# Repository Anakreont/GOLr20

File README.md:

# GOLr20 - HF balloon tracker with a receiver (FT8 contacts + WSPR)

One project, three parts: **GOLr20** - the tracker board (marked "R20" on the PCB), **GOLkf** - its firmware,
**GOLbase** - the ground station program.

The idea: a pico balloon that makes ordinary FT8 contacts (answers callers like a normal station), stores them in a log,
sends the log down in FT8 data frames, accepts signed commands from the ground and also beacons WSPR for tracking.

**Status (2026-11-23): boards v0.2 are ordered, nothing has been built or powered up yet. Board files and firmware are complete
enough to build and flash one, but the receiver, the transmitter level and the whole concept are unproven on hardware.**

## Hardware v0.2 (`pcb_v0.2/`)
- `R20_v0_2_gerber.zip`, `BOM_R20_v0_2.csv`, `CPL_R20_v0_2.csv` - the files sent to JLCPCB (Economic PCBA, top side, 0.8 mm).
- `kicad_src/` - KiCad 7 board (`pcb/r20.kicad_pcb`) and the Python scripts that generate it: `projekt.py` (parts and nets - there is no drawn schematic), `uklad.py` (placement), `buduj.py`. Parts placement drawing: `img/r20_v0_2_parts.png`.
- MCU RP2354A (QFN-60), 12 MHz crystal, USB for flashing (BOOTSEL), no SWD pads.
- Core supply from an external 1.1 V LDO (U8, TLV74311P) instead of the on-chip switcher: no inductor, less switching noise next to the receiver.
  VREG_FB to ground, VREG_LX open, VREG_AVDD/VREG_VIN powered (RP2350 datasheet, external core supply).
- TX: Si5351A + 26 MHz TCXO, CLK0 through 100 nF to the ANT pad; pads for an optional low-pass filter (C24, C25 not fitted).
- RX: ANT -> SN74CBTLV3253 used as a 4-phase mixer driven by Si5351 CLK1/CLK2 -> TLV9062 differential amplifiers -> ADC (I and Q).
- GPS ATGM336H and the Si5351/TCXO are behind P-MOSFET power switches. 3.3 V from ME6211C33.
- Solar input with pads for a supercapacitor (SC+ / SC-) on the bottom; D1 (clamp) not fitted.
- Break-off PROG tab with a 2x3 pin header: B0, EN, V+, D+, D-, G.
- GPIO: GPS UART 8 (TX) / 9 (RX), I2C 16 / 17, receiver supply from GPIO19, ADC0-2 for I, Q and panel voltage.
- Not fitted by design: C24, C25, D1.

### Known issues of v0.2
- The first BOM had a 1.2 V regulator for the core (ME6211C12). RP2350 recommends 1.05-1.16 V (absolute max 1.21 V).
  The BOM here already has the 1.1 V part (C485147, same SOT-23-5 pinout).
- Only 1 uF at DVDD (datasheet suggests 4.7 uF at the far pin).
- JLCPCB adds two 1.15 mm tooling holes for assembly (one under the GPS module, one in the ground pour). They do not cut any track.

## Firmware: GOLkf v0.2 (`firmware_golkf/`)
- `rdzen/` - the logic core, hardware independent: energy levels from panel voltage and sun elevation, window plan (TX/RX),
  FT8 contact state machine, log, signed commands, WSPR schedule (Traquito channel maths), no-transmit zones.
- `sprzet/` - hardware layer for R20 (Pico SDK): Si5351 control, I/Q receiver + FT8 decoder, FT8/WSPR transmit, GPS, flash storage, USB console.
- `uf2/` - prebuilt images to copy onto the RP2350 drive.
- **[`firmware_golkf/FLASHING.md`](firmware_golkf/FLASHING.md) - how to build, flash and bring the board up.**

**The firmware compiles and its PC-side tests pass, but it has never run on a board.** There is no power saving yet.
The command key (16 bytes) is not in the code; set it from the console (the same key goes into GOLbase).

## Ground station: GOLbase (`ground_station/`)
The program that receives the balloon's log and sends it commands through an ordinary HF radio (Windows, Python, Polish UI).
Balloon contacts are written to an ADIF file; Log4OM is optional. See [`ground_station/README.md`](ground_station/README.md).
`protocol/robot_proto.py` is a copy of the frame and command format (version 1) for reference.

## `sim_m33/` - can an RP2350 decode FT8 in time?
kgoba/ft8_lib built for Cortex-M33 and run in QEMU (mps2-an505) on recorded audio, counting instructions.
Busy 20 m recording: 19 decodes with default settings; with 70 candidates / 20 LDPC iterations 18 decodes and
about 85 million instructions after the window, estimated 0.7-1.0 s on a 150 MHz RP2350 (an estimate, not a measurement).

## `power_budget/`
`bilans.py` - rough current budget for six 52 x 23 mm cells in series and a mass estimate. Component currents are typical
values, not measurements.

## Callsigns
The callsigns in the code are placeholders (`QQ0QQQ` for WSPR, `QQ0Q` for FT8). Set your own before transmitting; an amateur licence is required.

## Related
GOLt433, the 433 MHz LoRa camera tracker from the same author: https://github.com/Anakreont/GOLt433

## Licence
MIT (see `LICENSE`) for the code and the board files. Design by SQ9GOL. Source comments are in Polish.

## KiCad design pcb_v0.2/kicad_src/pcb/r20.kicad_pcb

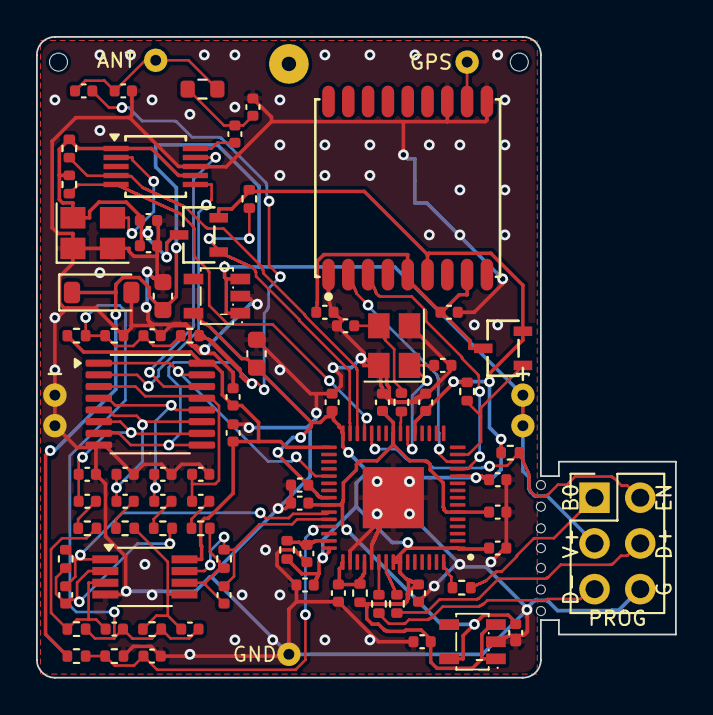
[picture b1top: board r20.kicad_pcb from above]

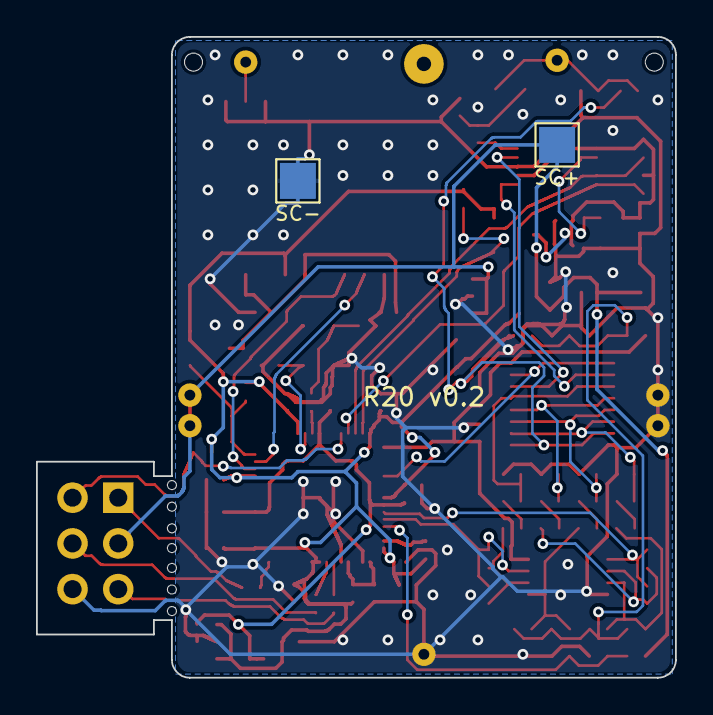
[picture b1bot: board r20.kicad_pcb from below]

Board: 2 copper layers, 35.5 x 35.6 mm, 99 parts (2 on the bottom side), 50 nets.

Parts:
ANT: (no value)
ANT_GND: (no value)
C1, C2: 10uF; C_0603_1608Metric
C3, C4, C5, C16, C22, C27, C37, C38, C40, C41, C42, C43: 1uF; C_0402_1005Metric
C6, C7, C8, C9, C10, C11, C12, C13, C14, C15, C20, C21, C23, C26, C28, C29, C30, C31, C36, C39: 100nF; C_0402_1005Metric
C17, C18: 15pF; C_0402_1005Metric
C24, C25: NC (filtr); C_0402_1005Metric
C32, C33, C34, C35: 47pF; C_0402_1005Metric
D1: NC BZT52C5V1 (ogr. 5,1 V, tylko pola); D_SOD-123
GPS_ANT: (no value)
H1, H2: (no value)
J1: PROG 2x3; PinHeader_2x03_P2.54mm_Vertical
L2: 0R (miejsce na cewke filtra); R_0603_1608Metric
MB1, MB2, MB3, MB4, MB5, MB6, MB7: (no value)
PV+, PV+2: (no value)
PV-, PV-2: (no value)
Q1: SI2301CDS (zas. Si5351 + TCXO); SI2301_SOT23
Q2: SI2301CDS (zas. GPS); SI2301_SOT23
R1, R2: 10R; R_0402_1005Metric
R3, R4, R16, R17, R20, R21: 1k; R_0402_1005Metric
R5, R13, R14: 10k; R_0402_1005Metric
R6, R7: 27R; R_0402_1005Metric
R8, R9, R18, R19, R22, R23: 1M; R_0402_1005Metric
R10, R15, R24: 100k; R_0402_1005Metric
R11, R12: 4.7k; R_0402_1005Metric
SC+: TestPoint_Pad_2.0x2.0mm
SC-: TestPoint_Pad_2.0x2.0mm
STAB: (no value)
U1: RP2354A (pamiec 2 MB w srodku); RP2354A_QFN-60
U3: SI5351A-B-GTR; MSOP-10_3x3mm_P0.5mm
U4: SN74CBTLV3253PWR; TSSOP-16_4.4x5mm_P0.65mm
U5: TLV9062IDGKR; VSSOP-8_3.0x3.0mm_P0.65mm
U6: ME6211C33M5G-N (3,3 V); ME6211_SOT23-5
U7: ATGM336H-5N31; ATGM336H
U8: ME6211C12M5G-N (rdzen 1,2 V); ME6211_SOT23-5
Y1: kwarc 12 MHz X322512MSB4SI; Crystal_SMD_3225-4Pin_3.2x2.5mm
Y2: TCXO 26 MHz KDS 1XTW26000MAA; Crystal_SMD_3225-4Pin_3.2x2.5mm

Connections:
+1V1: C4.1, C13.1, C14.1, C15.1, U1.6, U1.23, U1.39, U8.5
+3V3: C2.1, C3.1, C6.1, C7.1, C8.1, C9.1, C10.1, C11.1, C12.1, Q1.2, Q2.2, R1.1, R2.1, R5.2, R10.2, R24.2, U1.1, U1.11, U1.20, U1.30, U1.38, U1.45, U1.53, U1.54, U6.5, U7.6, U8.1, U8.3
ADC_AVDD: C16.1, R2.2, U1.44
ANT: ANT.1, C25.1, C26.1, L2.2
ANT_F: C23.2, C24.1, L2.1
BOOTSEL: J1.1, R4.2
GND: ANT_GND.1, C1.2, C2.2, C3.2, C4.2, C5.2, C6.2, C7.2, C8.2, C9.2, C10.2, C11.2, C12.2, C13.2, C14.2, C15.2, C16.2, C17.2, C18.2, C20.2, C21.2, C22.2, C24.2, C25.2, C27.2, C28.2, C29.2, C30.2, C31.2, C36.2, C37.2, C38.2, C39.2, D1.2, J1.6, PV-.1, PV-2.1, R9.2, R14.2, SC-.1, U1.47, U1.50, U1.61, U3.8, U4.8, U5.4, U6.2, U7.1, U7.10, U7.12, U8.2, Y1.2, Y1.4, Y2.1, Y2.2
GPS_ANT: GPS_ANT.1, U7.11
GPS_EN_N: Q2.1, R24.1, U1.14
GPS_RXD: U1.12, U7.3
GPS_TXD: U1.13, U7.2
GPS_VCC: C38.1, C39.1, Q2.3, U7.5, U7.8
I_N: C32.1, R17.2, R18.1, U5.2
I_P: C33.1, R16.2, R19.1, U5.3
LO_I: U3.9, U4.14
LO_Q: U3.6, U4.2
QA: C28.1, C40.1, U4.6, U4.10
QA_C: C40.2, R16.1
QB: C29.1, C42.1, U4.5, U4.11
QB_C: C42.2, R20.1
QC: C30.1, C41.1, U4.4, U4.12
QC_C: C41.2, R17.1
QD: C31.1, C43.1, U4.3, U4.13
QD_C: C43.2, R21.1
QSPI_SS: R4.1, U1.60
Q_N: C34.1, R21.2, R22.1, U5.6
Q_P: C35.1, R20.2, R23.1, U5.5
RF_EN_N: Q1.1, R10.1, U1.29
RF_VCC: C21.1, C22.1, Q1.3, R11.2, R12.2, U3.1, U3.7, Y2.4
RUN: J1.2, R5.1, U1.26
RX_BIAS: C27.1, C33.2, C35.2, R13.2, R14.1, R15.1, R19.2, R23.2
RX_I: C32.2, R18.2, U1.40, U5.1
RX_IN: C26.2, R15.2, U4.7, U4.9
RX_OE_N: U1.35, U4.1, U4.15
RX_PWR: C36.1, C37.1, R13.1, U1.31, U4.16, U5.8
RX_Q: C34.2, R22.2, U1.41, U5.7
SCL: R12.1, U1.28, U3.4
SDA: R11.1, U1.27, U3.5
TCXO_OUT: U3.2, Y2.3
TX_OUT: C23.1, U3.10
USB_DM: J1.5, R7.2
USB_DM_R: R7.1, U1.51
USB_DP: J1.4, R6.2
USB_DP_R: R6.1, U1.52
VREG_F: C5.1, R1.2, U1.46, U1.49
VSC: C1.1, D1.1, J1.3, PV+.1, PV+2.1, R8.1, SC+.1, U6.1, U6.3
VSC_ADC: C20.1, R8.2, R9.1, U1.42
XIN: C17.1, U1.21, Y1.1
XOUT: C18.1, R3.2, Y1.3
XOUT_R: R3.1, U1.22

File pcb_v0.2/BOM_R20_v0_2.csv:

Comment,Designator,Footprint,LCSC Part #
10uF,"C1,C2",0603,C19702
1uF,"C3,C4,C5,C16,C22,C27,C37,C38,C40,C41,C42,C43",0402,C52923
100nF,"C6,C7,C8,C9,C10,C11,C12,C13,C14,C15,C20,C21,C23,C26,C28,C29,C30,C31,C36,C39",0402,C1525
15pF,"C17,C18",0402,C1548
47pF,"C32,C33,C34,C35",0402,C1567
0R,L2,0603,C21189
SI2301CDS,"Q1,Q2",SOT-23,C10487
10R,"R1,R2",0402,C25077
1k,"R3,R4,R16,R17,R20,R21",0402,C11702
10k,"R5,R13,R14",0402,C25744
27R,"R6,R7",0402,C25100
1M,"R8,R9,R18,R19,R22,R23",0402,C26083
100k,"R10,R15,R24",0402,C25741
4.7k,"R11,R12",0402,C25900
RP2354A,U1,QFN-60-1EP_7x7mm_P0.4mm,C41378174
SI5351A-B-GTR,U3,MSOP-10,C504891
SN74CBTLV3253PWR,U4,TSSOP-16,C105246
TLV9062IDGKR,U5,VSSOP-8,C398356
ME6211C33M5G-N,U6,SOT-23-5,C82942
ATGM336H-5N31,U7,ATGM336H,C90770
TLV74311PDBVR 1.1V,U8,SOT-23-5,C485147
kwarc 12 MHz X322512MSB4SI,Y1,SMD3225-4P,C9002
TCXO 26 MHz KDS 1XTW26000MAA,Y2,SMD3225-4P,C213404

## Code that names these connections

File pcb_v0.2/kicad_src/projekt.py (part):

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      # pamiec 2 MB jest w obudowie RP2354A (piny QSPI 55-59 zostaja niepodlaczone na plytce)
      # przydzial GPIO pod rozmieszczenie (U1 obrocony o 180 st.: piny 31-45 w strone odbiornika, 16-30 w strone GPS)
      2: None, 3: None, 4: None, 5: None, 7: None, 8: None, 9: None, 10: None,          # GPIO0-7 wolne
      # 21.11 23:20: GPS przeniesiony na prawy bok ukladu, I2C i RF_EN_N na gorny - przy pinach 16-19 i 32-34 sciezki sie nie miescily
      12: "GPS_RXD",      # GPIO8  UART1 TX -> RXD GPS
      13: "GPS_TXD",      # GPIO9  UART1 RX <- TXD GPS
      14: "GPS_EN_N",     # GPIO10 stan niski = GPS wlaczony (Q2)
      15: None,           # GPIO11 wolny
      16: None, 17: None, 18: None, 19: None,                                             # GPIO12-15 wolne
      21: "XIN", 22: "XOUT_R",
      24: None, 25: None, 26: "RUN",        # SWCLK / SWD bez pol (wgrywanie przez USB)
      27: "SDA",          # GPIO16 I2C0 SDA
      28: "SCL",          # GPIO17 I2C0 SCL
      29: "RF_EN_N",      # GPIO18 stan niski = Si5351 + TCXO wlaczone (Q1)
      31: "RX_PWR",       # GPIO19 zasilanie odbiornika (klucz + wzmacniacz, ok. 3 mA) wprost z pinu
      32: None, 33: None, 34: None,                                                       # GPIO20-22 wolne
      35: "RX_OE_N",      # GPIO23 stan niski = klucz odbiornika wlaczony; przy nadawaniu 1 (klucz odlaczony od anteny)
      36: None, 37: None,                                                                 # GPIO24-25 wolne
      40: "RX_I",         # GPIO26 ADC0
      41: "RX_Q",         # GPIO27 ADC1
      42: "VSC_ADC",      # GPIO28 ADC2  napiecie paneli / 2
      43: None,           # GPIO29 ADC3 wolny
      44: "ADC_AVDD",
      46: "VREG_F", 47: "GND", 48: None, 49: "VREG_F", 50: "GND",    # wbudowana przetwornica nieuzywana: LX wolny, FB do masy (karta RP2350, zewn. zasilanie rdzenia)
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SI = {1: "RF_VCC", 2: "TCXO_OUT", 3: None, 4: "SCL", 5: "SDA", 6: "LO_Q", 7: "RF_VCC", 8: "GND", 9: "LO_I", 10: "TX_OUT"}
TCXO = {1: "GND", 2: "GND", 3: "TCXO_OUT", 4: "RF_VCC"}        # 1 = OE# (stan niski = wlaczony), jak w ICT v3.61
# SN74CBTLV3253 TSSOP-16: obie polowki rownolegle (mniejsza rezystancja klucza); S0 = LO_I, S1 = LO_Q (przesuniete o 90 st.)
MUX = {1: "RX_OE_N", 15: "RX_OE_N",              # OE# obu polowek z GPIO23 (przy nadawaniu = 1, inaczej klucz zwiera antene przez kondensatory odbiornika)
       14: "LO_I", 2: "LO_Q",
       7: "RX_IN", 9: "RX_IN",
       6: "QA", 10: "QA", 5: "QB", 11: "QB", 4: "QC", 12: "QC", 3: "QD", 13: "QD",   # B1..B4 = 4 fazy probkowania
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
